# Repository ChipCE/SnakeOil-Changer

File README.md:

# SnakeOil-Changer
Heavyduty base platform for toolchanger. Lightweight cartesian kinematic, quad independent  Z.

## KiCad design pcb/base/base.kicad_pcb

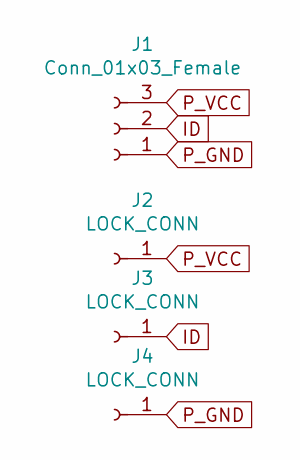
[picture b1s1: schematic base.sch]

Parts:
J1: Conn_01x03_Female; tool-plate-input-conn
J2, J3, J4: LOCK_CONN; tool-plate-ball-conn

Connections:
ID: J1.2, J3.1
P_GND: J1.1, J4.1
P_VCC: J1.3, J2.1

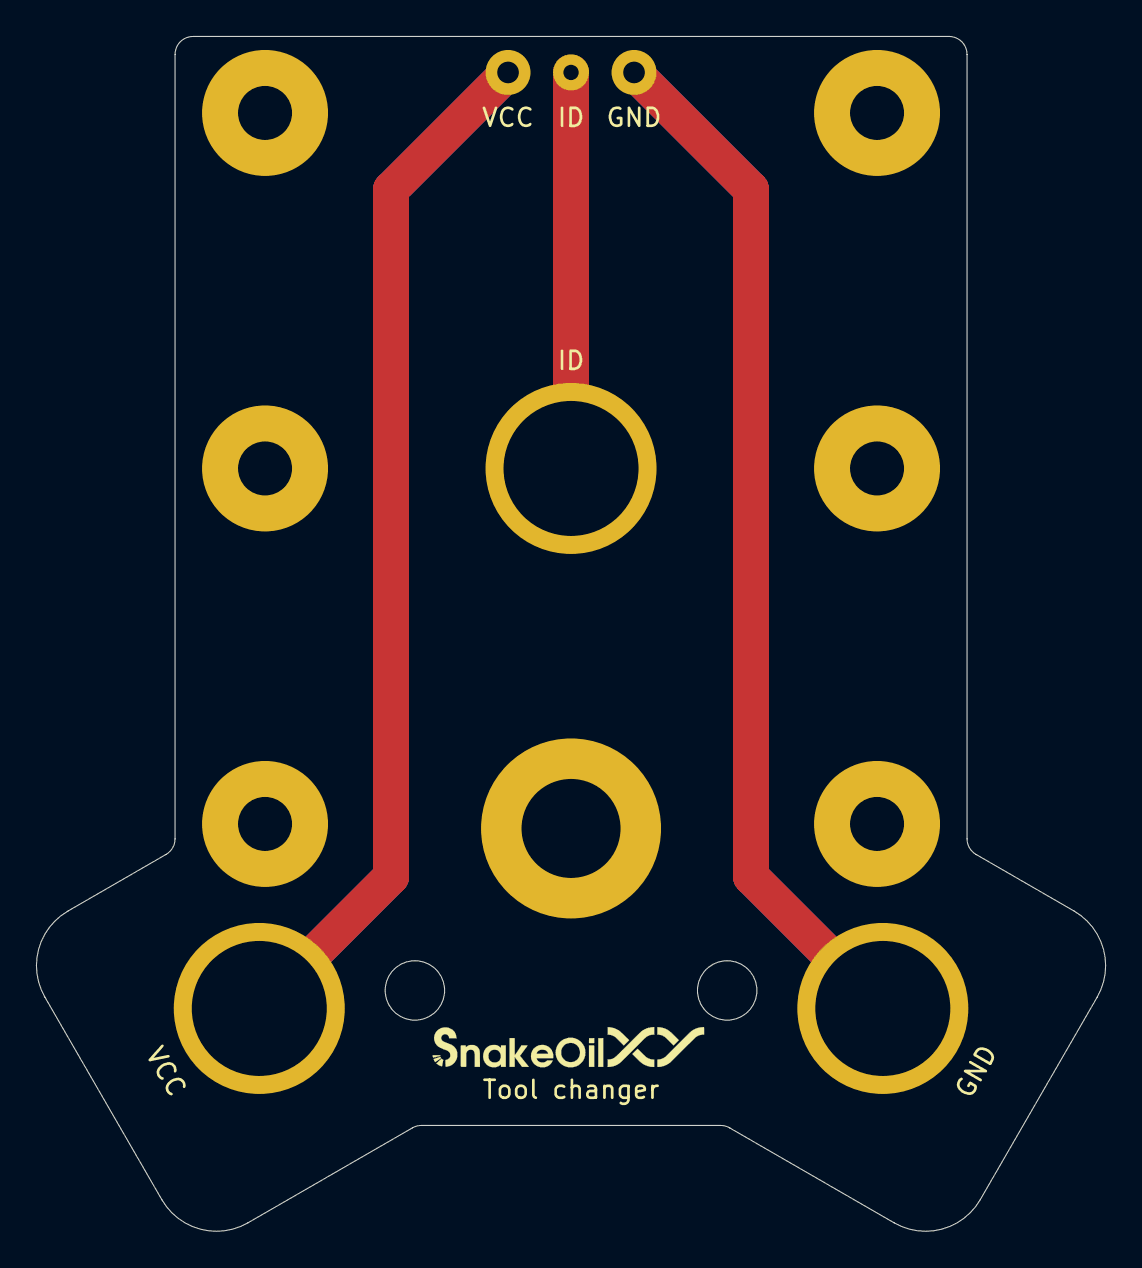
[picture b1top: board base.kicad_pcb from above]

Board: 2 copper layers, 59.4 x 66.4 mm, 4 parts (0 on the bottom side), 3 nets.

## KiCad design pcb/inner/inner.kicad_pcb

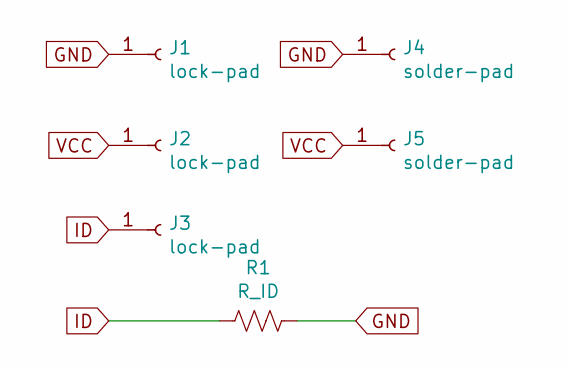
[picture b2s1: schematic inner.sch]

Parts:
J1, J2: lock-pad; tool-plate-lock-pad
J3: lock-pad; tool-plate-lock-pad-single-side
J4, J5: solder-pad; tool-plate-solder-pad
R1: R_ID; R_0805_2012Metric_Pad1.20x1.40mm_HandSolder

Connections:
GND: J1.1, J4.1, R1.2
ID: J3.1, R1.1
VCC: J2.1, J5.1

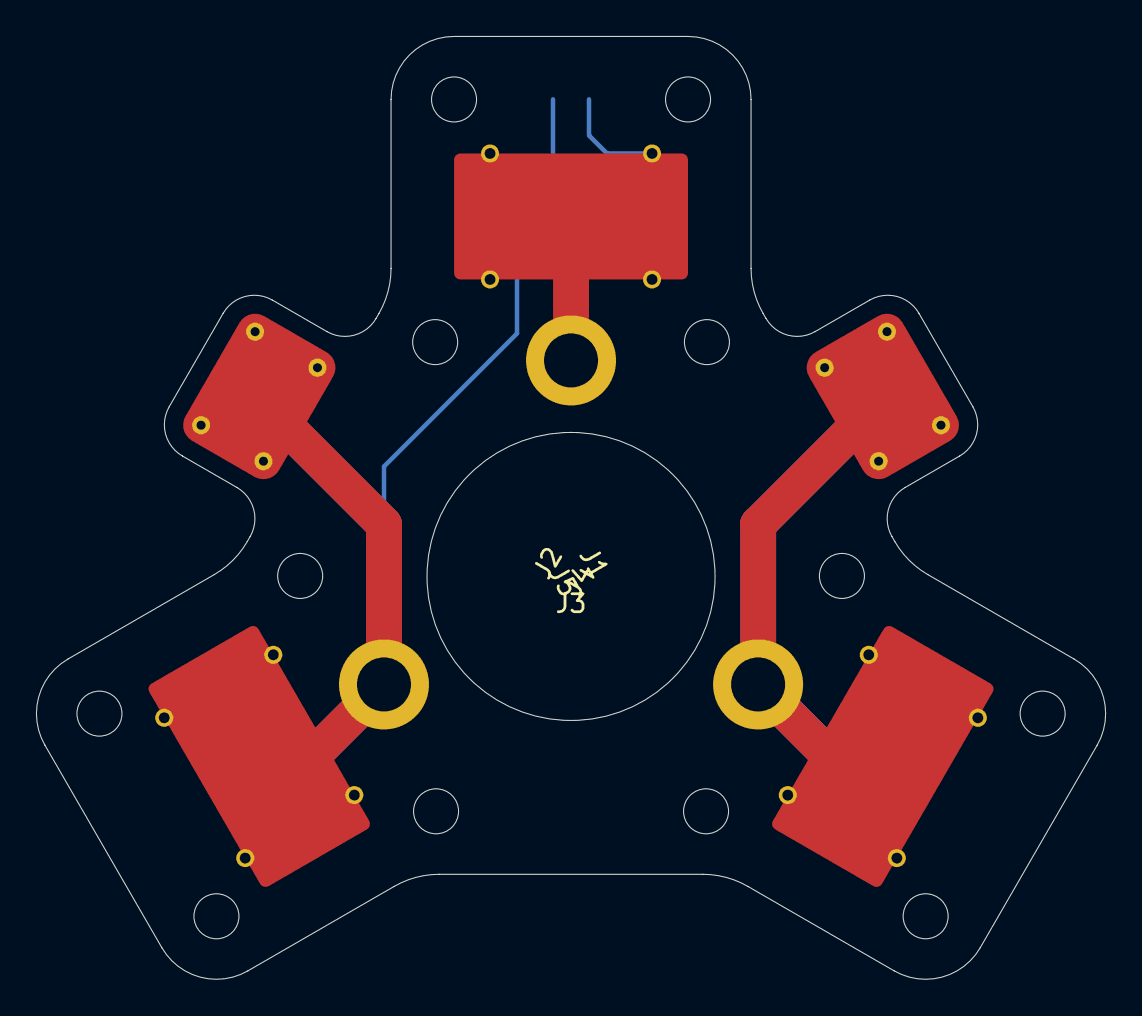
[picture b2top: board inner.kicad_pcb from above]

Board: 2 copper layers, 59.4 x 52.4 mm, 6 parts (1 on the bottom side), 3 nets.

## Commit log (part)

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2024-02-20 init
2024-02-20 add draft layout
2024-02-21 sync
2024-02-22 change gantry base layout
2026-01-09 ganty export
2026-04-17 change folder structure
